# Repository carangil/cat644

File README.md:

cat644
======

Cat-644 is a microcomputer based around the Atmega644 microcontroller.  This repository will hold both hardware designs and software source code.

dirs:

schematics/  	hardware information
cat1/  			OLD hardware test routines.  Will be deleted when CAT-OS is finished
cat-os/			'scratchpad' OS.  Being built out of code in the cat1 directory

LICENSE

All code is under GPL v2.  See LICENSE file for details.

All code written by Mark Sherman, with a few exceptions:

'wait until' function taken from arduino-tvout: http://code.google.com/p/arduino-tvout/  (License: MIT License)

The 'general idea' of VGA generation from an AVR was taken from these resources:
http://www.lucidscience.com/pro-vga%20video%20generator-1.aspx
http://quinndunki.com/blondihacks/?p=955
http://avga.prometheus4.com/

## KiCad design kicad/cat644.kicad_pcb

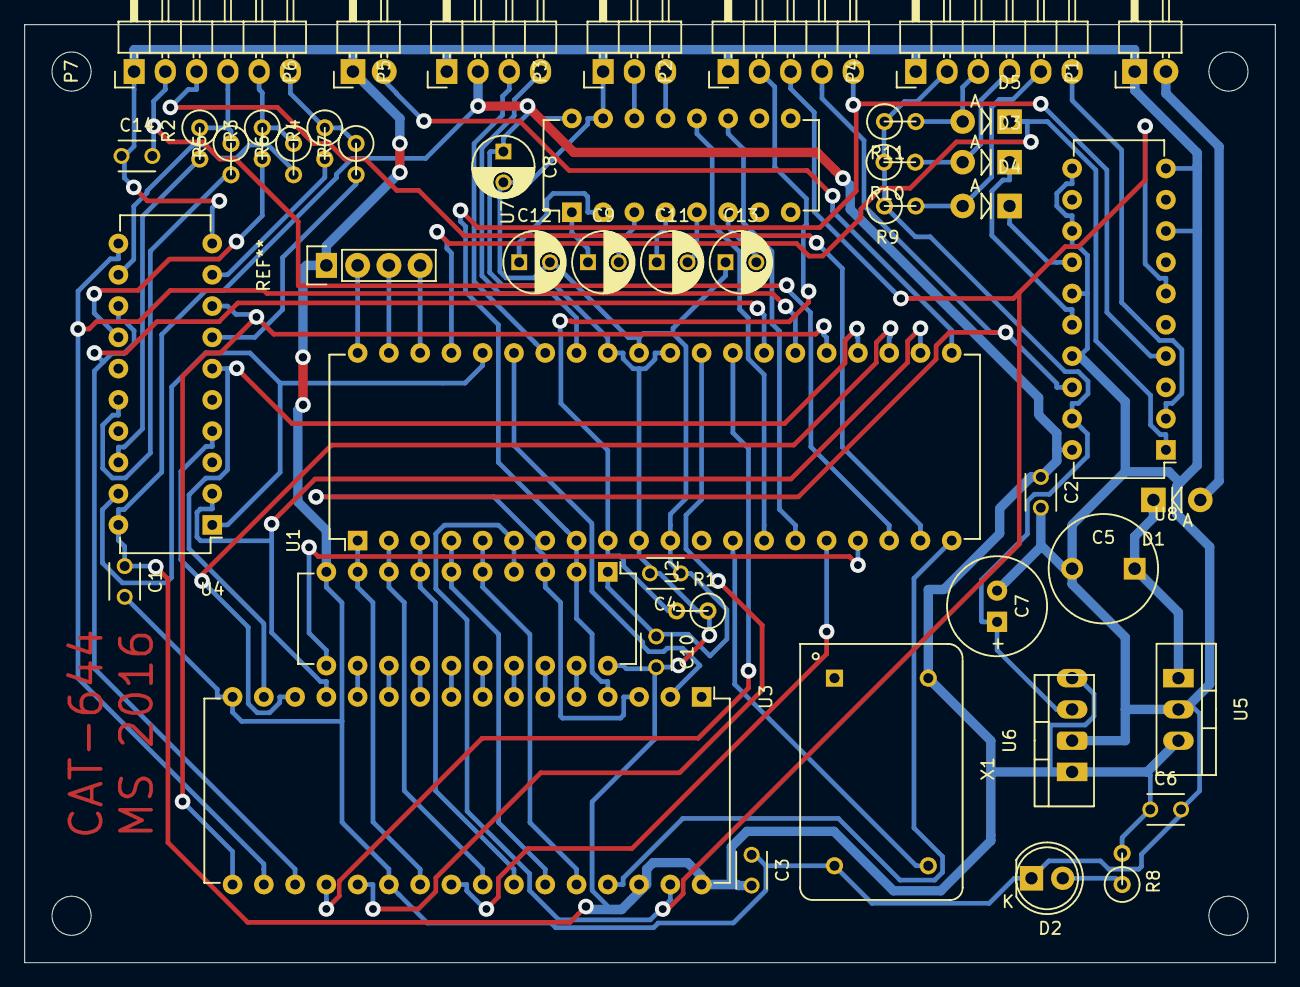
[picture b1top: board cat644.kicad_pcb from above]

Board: 2 copper layers, 101.6 x 76.2 mm, 50 parts (0 on the bottom side), 68 nets.

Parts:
C1, C2, C3, C4, C10: 0.1uF; C_Disc_D3_P2.5
C5: 470uF; C2V8
C6: 0.1 uF; C_Disc_D3_P2.5
C7: 2.2 uF; C1V8
C8: 10uF; C_Radial_D5_L11_P2.5
C9, C11, C12, C13: 1uF; C_Radial_D5_L11_P2.5
C14: 0.01uF; C_Disc_D3_P2.5
D1: 1N4001; Diode_DO-41_SOD81_Vertical_AnodeUp
D2: LED; LED-5MM
D3, D4, D5: D; Diode_DO-41_SOD81_Vertical_AnodeUp
P1: PWR; Pin_Header_Angled_1x02
P2: ISP; Pin_Header_Angled_1x05
P3: SER; Pin_Header_Angled_1x03
P4: SD; Pin_Header_Angled_1x06
P5: PS2; Pin_Header_Angled_1x04
P6: AUD; Pin_Header_Angled_1x02
P7: VGA; Pin_Header_Angled_1x06
R1: 10k; R1
R2, R3, R4: 1k; R1
R5, R6, R7, R8: 470; R1
R9, R10, R11: 5k; R1
U1: ATMEGA644-P; DIP-40_W15.24mm
U2: 74LS573; DIP-20_W7.62mm
U3: 628128; DIP-32_W15.24mm
U4, U8: 74LS244; DIP-20_W7.62mm
U5: 7805; TO-220_Neutral123_Vertical
U6: LF33; TO-220_Neutral123_Vertical
U7: MAX232; DIP-16_W7.62mm
X1: OSC 20MHz; KXO-200
mh1, mh2, mh3, mh4: MountingHole_3.5mm

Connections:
/av/AUDIO_OUT: P6.2, U1.21
/av/HSYNC: P7.3, U1.19
/av/VGA_BLUE: P7.6, R4.1, R7.1
/av/VGA_GREEN: P7.5, R3.1, R6.1
/av/VGA_RED: P7.4, R2.1, R5.1
/av/VSYNC: C14.2, P7.2, U1.18
/serial/MISO: P2.4, U1.7, U2.3, U3.3, U8.18
/serial/MOSI: P2.3, U1.6, U2.4, U3.31, U8.6
/serial/PS2_DATA: P5.3, U1.34
/serial/PS2_DK: P5.4, U1.33
/serial/RESET: P2.2, R1.2, U1.9
/serial/RX1_OUT: U1.14, U7.12
/serial/SCLK: P2.5, U1.8, U2.2, U3.4, U8.4
/serial/SD_ENABLE: D5.1, U1.37, U8.1
/serial/TX1_IN: U1.15, U7.11
GND: C1.2, C2.2, C3.1, C4.1, C5.2, C6.2, C7.2, C8.2, C10.1, C12.2, C13.1, C14.1, D2.1, P1.1, P2.1, P3.1, P4.1, P5.1, P6.1, P7.1, U1.11, U1.31, U2.1, U2.10, U3.16, U3.22, U4.10, U5.2, U6.2, U7.15, U8.8, U8.10, U8.11, U8.13, U8.15, U8.17, X1.7
unnamed: C5.1, D1.1, U5.1
unnamed: C9.1, U7.1
unnamed: C9.2, U7.3
unnamed: C11.1, U7.4
unnamed: C11.2, U7.5
unnamed: C12.1, U7.2
unnamed: C13.2, U7.6
unnamed: D1.2, P1.2
unnamed: D2.2, R8.1
unnamed: D3.1, U8.16
unnamed: D3.2, P4.4, R10.2
unnamed: D4.1, U8.14
unnamed: D4.2, P4.5, R9.2
unnamed: D5.2, P4.3, R11.2
unnamed: P3.2, U7.14
unnamed: P3.3, U7.13
unnamed: P4.6, U8.2
unnamed: R2.2, U4.18
unnamed: R3.2, U4.14
unnamed: R4.2, U4.9
unnamed: R5.2, U4.16
unnamed: R6.2, U4.12
unnamed: R7.2, U4.7
unnamed: U1.1, U2.9, U3.23
unnamed: U1.2, U2.8, U3.25
unnamed: U1.3, U2.7, U3.26
unnamed: U1.4, U2.6, U3.27
unnamed: U1.5, U2.5, U3.28
unnamed: U1.13, X1.8
unnamed: U1.16, U3.24
unnamed: U1.17, U2.11
unnamed: U1.20, U3.29
unnamed: U1.22, U3.13, U4.2
unnamed: U1.23, U3.14, U4.4
unnamed: U1.24, U3.15, U4.6
unnamed: U1.25, U3.17, U4.8
unnamed: U1.26, U3.18, U4.11
unnamed: U1.27, U3.19, U4.13
unnamed: U1.28, U3.20
unnamed: U1.29, U3.21
unnamed: U1.35, U3.2
unnamed: U1.36, U4.1, U4.19
unnamed: U2.12, U3.12
unnamed: U2.13, U3.11
unnamed: U2.14, U3.10
unnamed: U2.15, U3.9
unnamed: U2.16, U3.8
unnamed: U2.17, U3.7
unnamed: U2.18, U3.6
unnamed: U2.19, U3.5
VCC: C1.1, C2.1, C3.2, C4.2, C6.1, C8.1, C10.2, P5.2, R1.1, R8.2, U1.10, U1.30, U1.32, U2.20, U3.30, U3.32, U4.20, U5.3, U6.1, U6.4, U7.16, U8.20, X1.14
VDD: C7.1, P4.2, R9.1, R10.1, R11.1, U6.3, U8.19

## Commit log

2014-08-19 Initial checkin of code.
2014-08-19 Update readme.
2016-11-02 update schematics. move cat-os to cat-1 to get ready for update
2016-11-02 Bring in the new cat-os
2016-11-02 kicad project
2016-11-07 updated pcb
2016-11-10 updated pcb
    changed vias to 0.05/0.027 dia/drill
    track size increased to 0.015
    filter caps added to regulator outputs
2016-11-24 bring in sd card routines
2016-11-24 Switch hsync and vsync lines for an upcoming optimization
2016-11-28 updated pcb with header on unused pins and extra pad for 117 regulator
2018-09-03 old uncommited changes - saving for now
2018-09-03 Start new OS project: kittyOS. Testing with simavr. Can read and write serial port thru a chardevice wrapper. Can run a 'userland' program/function and pass it a chardevice to interact with.
2018-09-04 XRAM working on both hardware and simavr. needed to modify simavr memcpyi2x and memcpyx2i copied between internal and external sram. memcpy*2* takes 16 bit addresses. User still needs to select which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
2018-09-06 adding in vga driver. also trying to rewrite a basic vga driver in assembly instead of C to get better control of timing.
2018-09-07 vga fullscreen working w/ horizontal and vertical scrolling, and limited vertical window
    todo:
    enable oddonly 'fast mode'
    enable limited horizontal window for horz scrolling
    need to reimplement ps2 polling: the original cat1 demo program used polled the ps2 inputs once per scanline to avoid interrupt conflicts
2018-09-07 added 'skippy' video mode which draws every other video line, and gives about 50% of the cpu back to the main program
    TODO: still need to add in ps2keyboard polling.
    idea for polling: the original cat1 demo driver sampled at around hsync (the same time each line), and then if the sample showed a change, at the END of the scanline, it handled the key. I did this i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
    For now, if it shows a change, lets just aboirt the current line. it'll disrupt the display, but whatever.
    Also might be able to just 'notch' the display off t
2018-09-12 fix 525 lines scanlines instead of 512
2018-09-13 experimenting with replacing some of the pixel output code with NOPs if I can do the same thing but with some of the instructions nops, then the nops can be replaced with something useful
2018-09-14 remove port manipulation I was messing around with to test in simavr
2018-09-14 saving some code here that messes with Timer 0, which might be used as a hardware bit flipper for some pixels
2018-09-18 reading keyboard OK, but it glitches screen (counter bug)
2018-09-18 fix video line counting when accepting keypressed. still blanks out lines, but keeps timing OK
2018-09-18 just formatting and commenting found a bug, but commented instead of fixing. part of this was to rebuild and make sure the hexfile didn't change at all. This is purely a formatting commit to make the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
2018-09-19 fix ram bank bug (probably) fix keybuffer increment bug add reading keyboard is raw chardevice (get scancodes)
2018-09-20 Capture keyboard port state and change flag at front of the line routine. Active scanlines are shortened to handle the keyboard. Screen is indisturbed when typing. TODO: When there is no keyboard act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
    Test starts in vidfull (The HARD case, because there's no blank lines to abuse)
    Test ends wth
2018-09-21 VGA and keyboard work together better now. Pressing a key only notches out the rightmost 32 pixels of a scanline.
    intvga-bad.s contains an experimental version that doesn't quite work properly yet. It should let the keyboard be read during horizontal blanking by not returning to the user program. But its acting 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
2018-09-22 keyboard without disrupting display keyboard can decode to ascii characters including shift and arrows vga console output (draws characters to screen) w/ LF and vertical scrolling
2018-09-24 forgot a file
2018-09-24 Bring in old spi driver from abandoned catos
2018-09-26 split spi_inout into a read and write function. Tested in simulator, the AVR still spend time waiting for the transfer to finish. Except now, there's the possible to write, and then the program can d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
2018-09-26 add in cat-os sdcard driver, and modify for kittyos. Only so far tested the sdcard init function, which returns the correct size of the sdcard (so I guess it works?)
    fixed some ps2 warnings
2018-09-27 copying interpreter.s from hack-interpreter (which was never a git project :-( ) hack-interpreter was written a year (or two?) to test how fast of an interpreter I could write for AVR renaming it to 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
    6 AVR clocks to interpret a 16-bit reg,reg add.
    The 8088 took 3 clocks, but only ran at 4.77 mhz.
2018-09-27 runs a small program inside bytecode interpreter (adds two numbers, outputs via dummy syscall) also checking in the cross assembler
    this interpreter and assembler was originally prototyped a long time ago
    but now its finally in
2018-09-30 routines that write to screen set to video bank (A16LOW) main mux and 'findDevice' function disable debug messages from keyboard routines (for now; it seems to work) syscall from interpreter simple i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
2018-09-30 Retrochallenge 2018/09 stopping point.
2019-03-17 Fix newline bug rename vga-bad to vga-speg add build date/time
2019-03-20 add mmalloc, xmalloc,
2019-03-24 Support allocating memory by handle Support reference counting 'grabbed' handle blocks
2022-10-09 check in old changes that never made it to git
2022-11-07 Committing changes for the retrochallenge 2022/10 This includes 1 bugfix made after the competition ended: SDCard CS line handling... sometimes caused things to fail
